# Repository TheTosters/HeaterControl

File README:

# Preamble
first instruction taken from:
https://github.com/Polidea/cmake-nRF5x
It is constantly changed and improved (or downproved :P)

# IMPORTANT:
Toolchain:
 * gcc-arm-none-eabi-8-2018-q4-major, or
 * gcc-arm-none-eabi-8-2019-q3-update-linux

NRF SDK:
 * nRF5_SDK_15.2.0_9412b96

You also need nrfprog tools and small patch for SDK from CMSIS.
But this is handled by preapre_env.sh

# To build & run tests...

This is super-glue solution, so your eyes will bleeed...
It will use host compiler (not cross-compiler) to build host based tests.
It is NOT ment to test all, only most complicated logic. So to have test build and run you have to:

execute:
cmake .. -DBUILD_TESTS=ON
make all

then you can call for example
./test/time_schedule_tests

# Manual patching SDK
But if you set C++17 then it fails :P You have to manualy patch NordicSDK (15.2)
and upgrade CMSIS to have things working go here
https://github.com/ARM-software/CMSIS_5

and download following files which should be placed here:
libarm_cortexM4lf_math.a, libarm_cortexM4l_math.a  ->  nordic_SDK_15.2/components/toolchain/cmsis/dsp/GCC
arm_cortexM4lf_math.lib  arm_cortexM4l_math.lib  ->  nordic_SDK_15.2/components/toolchain/cmsis/dsp/ARM

also copy folder 
CMSIS_5-develop/CMSIS/Core/Include  ->  nordic_SDK_15.2/components/toolchain/cmsis/include

clean & build all should work

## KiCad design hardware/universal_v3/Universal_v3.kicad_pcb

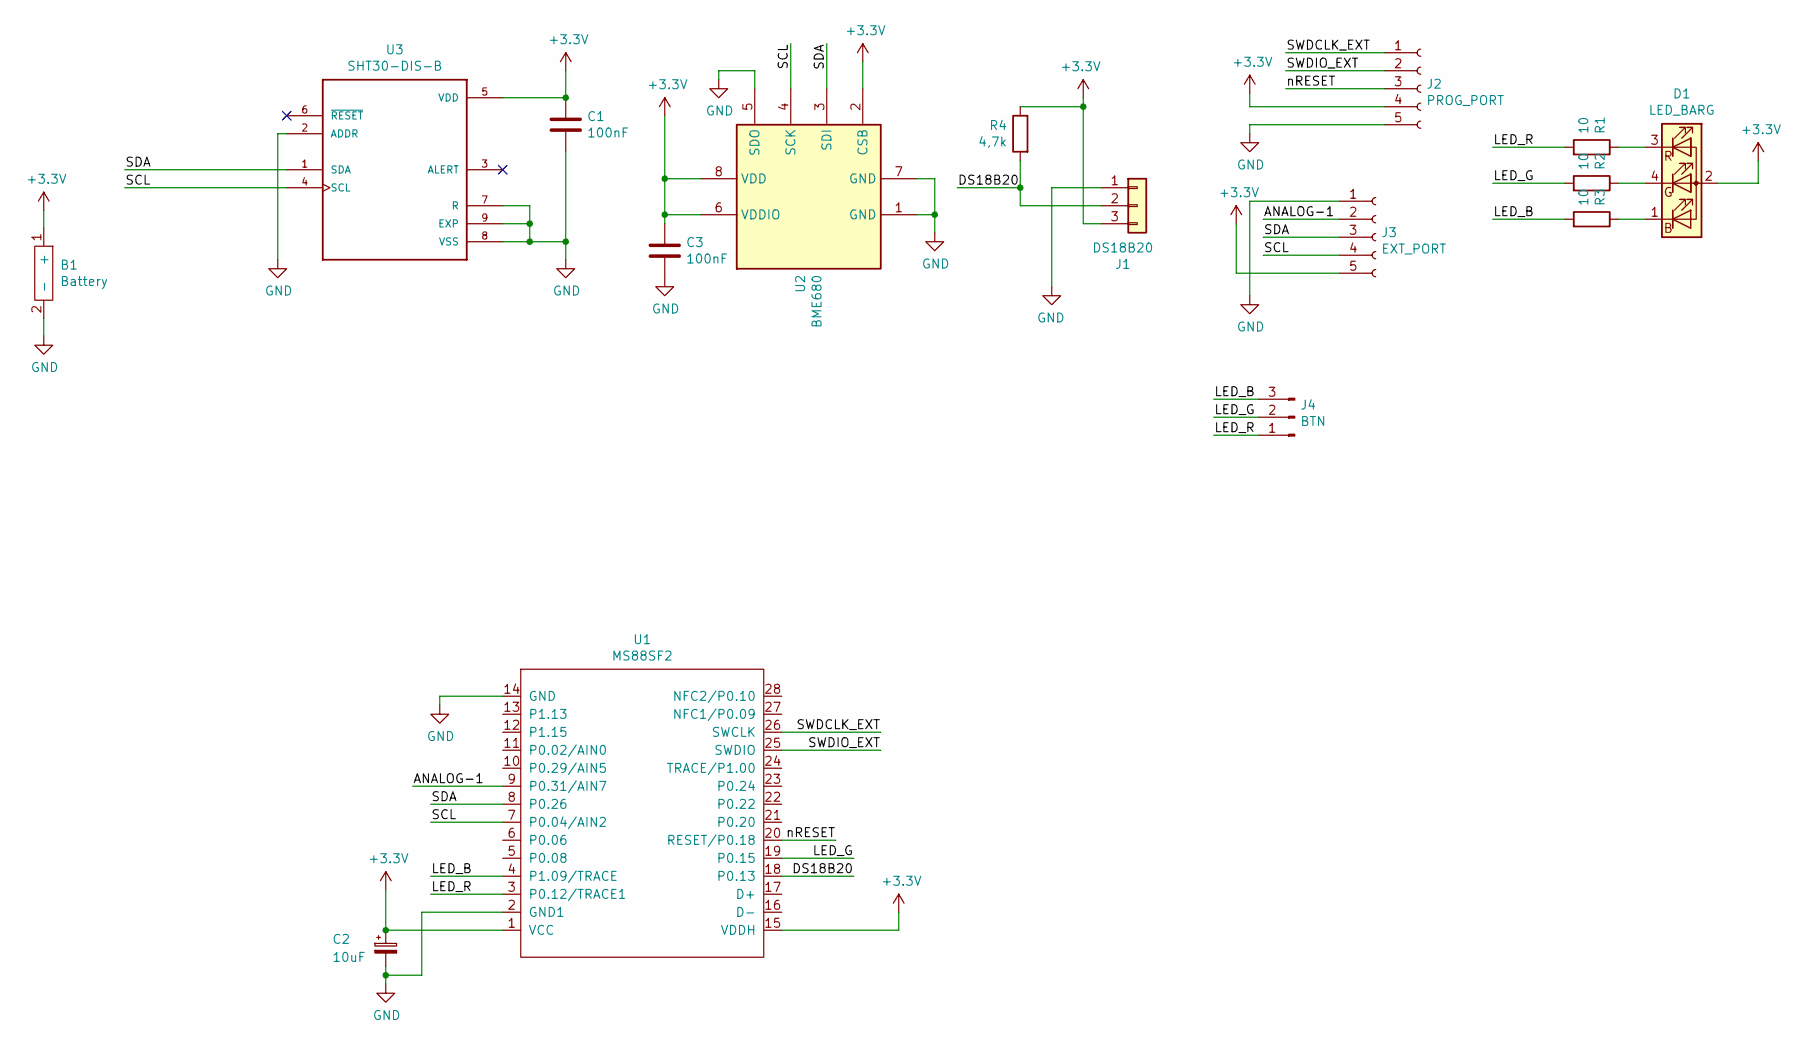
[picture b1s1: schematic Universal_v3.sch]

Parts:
B1: Battery; Cr2032-Holder
C1, C3: 100nF; C_0402_1005Metric
C2: 10uF; CP_EIA-2012-12_Kemet-R
D1: LED_BARG; Everlight_19-237_R6GHBHC-M07_2T
J1: DS18B20; 3Pads
J2: PROG_PORT; 5xPad
J3: EXT_PORT; 5xPad
J4: BTN; PinHeader_1x03_P2.54mm_Vertical
R1, R2, R3: 10; R_0402_1005Metric
R4: 4,7k; R_0402_1005Metric
U1: MS88SF2
U2: BME680; Bosch_LGA-8_3x3mm_P0.8mm_ClockwisePinNumbering
U3: SHT30-DIS-B; DFN250X250X100-9N

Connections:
+3V3: B1.1 (+), C1.1, C2.1, C3.1, D1.2 (A), J1.3, J2.4, J3.5, R4.1, U1.1 (VCC), U1.15 (VDDH), U2.2 (CSB), U2.6 (VDDIO), U2.8 (VDD), U3.5 (VDD)
/ANALOG-1: J3.2, U1.9 (P0.31/AIN7)
/DS18B20: J1.2, R4.2, U1.18 (P0.13)
/LED_B: J4.3, R3.2, U1.4 (P1.09/TRACE)
/LED_G: J4.2, R2.2, U1.19 (P0.15)
/LED_R: J4.1, R1.2, U1.3 (P0.12/TRACE1)
/SCL: J3.4, U1.7 (P0.04/AIN2), U2.4 (SCK), U3.4 (SCL)
/SDA: J3.3, U1.8 (P0.26), U2.3 (SDI), U3.1 (SDA)
/SWDCLK_EXT: J2.1, U1.26 (SWCLK)
/SWDIO_EXT: J2.2, U1.25 (SWDIO)
/nRESET: J2.3, U1.20 (RESET/P0.18)
GND: B1.2 (-), C1.2, C2.2, C3.2, J1.1, J2.5, J3.1, U1.2 (GND1), U1.14 (GND), U2.1 (GND), U2.5 (SDO), U2.7 (GND), U3.2 (ADDR), U3.7 (R), U3.8 (VSS), U3.9 (EXP)
unnamed: D1.1 (BK), R3.1
unnamed: D1.3 (RK), R1.1
unnamed: D1.4 (GK), R2.1

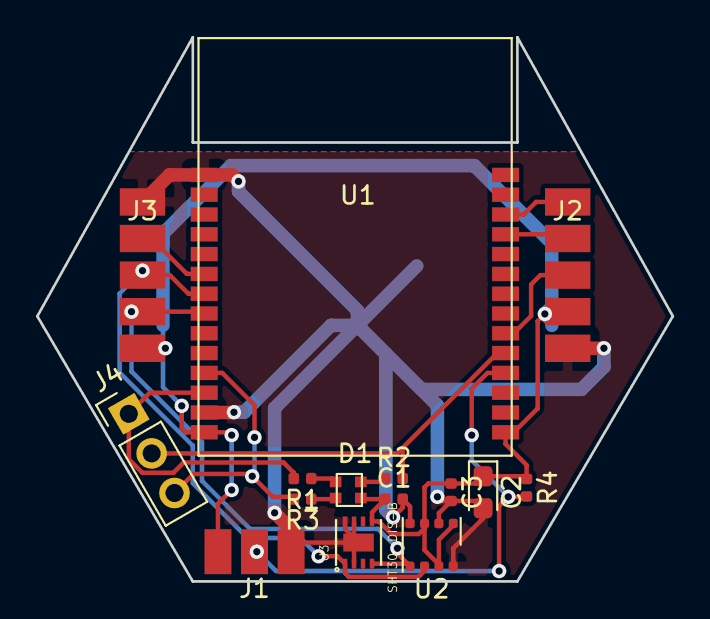
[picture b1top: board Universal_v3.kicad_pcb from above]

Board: 2 copper layers, 35.3 x 30.2 mm, 16 parts (1 on the bottom side), 15 nets.

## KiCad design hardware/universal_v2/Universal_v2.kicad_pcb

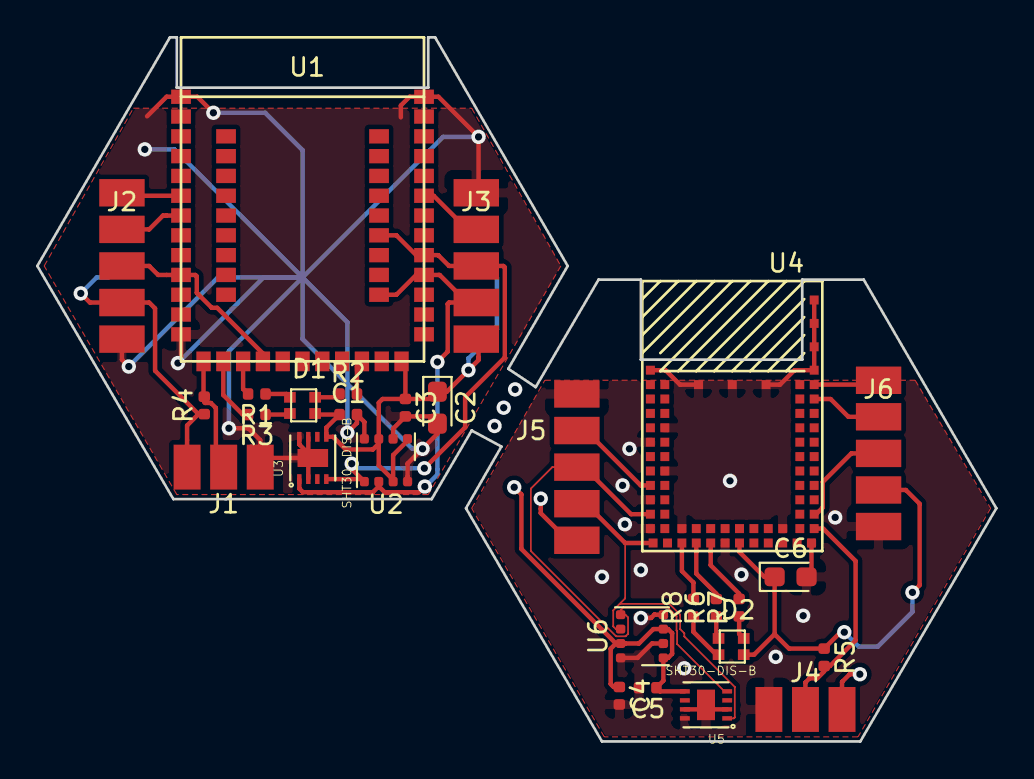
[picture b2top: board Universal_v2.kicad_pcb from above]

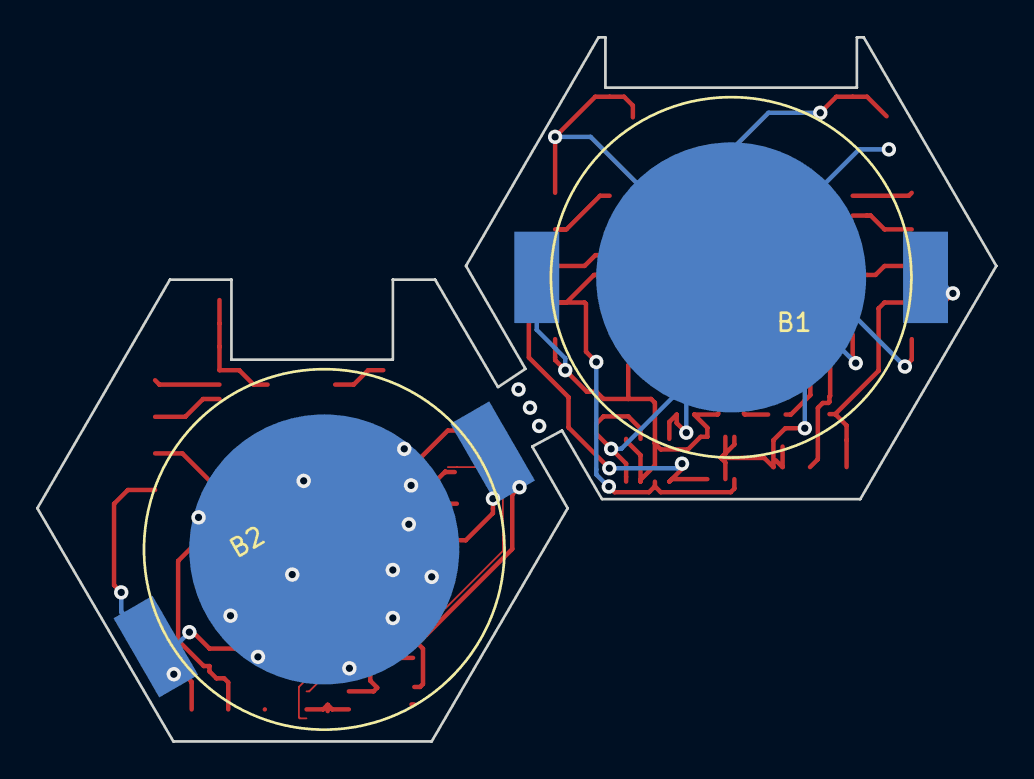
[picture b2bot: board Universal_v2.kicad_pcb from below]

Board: 2 copper layers, 53.3 x 39.1 mm, 30 parts (2 on the bottom side), 28 nets.

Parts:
B1, B2: Battery; Cr2032-Holder
C1, C3, C4, C5: 100nF; C_0402_1005Metric
C2, C6: 10uF; CP_EIA-2012-12_Kemet-R
D1, D2: LED_BARG; Everlight_19-237_R6GHBHC-M07_2T
J1, J4: DS18B20; 3Pads
J2, J6: PROG_PORT; 5xPad
J3, J5: EXT_PORT; 5xPad
R1, R2, R3, R6, R7, R8: 10; R_0402_1005Metric
R4, R5: 4,7k; R_0402_1005Metric
U1: HolyIot-18010; HolyIot_18010
U2, U6: BME680; Bosch_LGA-8_3x3mm_P0.8mm_ClockwisePinNumbering
U3, U5: SHT30-DIS-B; DFN250X250X100-9N
U4: BL654

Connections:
+3V3: B1.1, B2.1, C1.1, C2.1, C3.1, C4.1, C5.1, C6.1, D1.2, D2.2, J1.3, J2.4, J3.5, J4.3, J5.5, J6.4, R4.1, R5.1, U1.55, U2.2, U2.6, U2.8, U3.5, U4.31, U5.5, U6.2, U6.6, U6.8
/ANALOG-1: J3.2, U1.6
/DS18B20: J1.2, R4.2, U1.45
/LED_B: R3.2, U1.46
/LED_G: R2.2, U1.53
/LED_R: R1.2, U1.47
/Laird/ANALOG-1: J5.2, U4.49
/Laird/DS18B20: J4.2, R5.2, U4.21
/Laird/LED_B: R8.2, U4.39
/Laird/LED_G: R7.2, U4.35
/Laird/LED_R: R6.2, U4.37
/Laird/SCL: J5.3, U4.45, U5.4, U6.4
/Laird/SDA: J5.4, U4.42, U5.1, U6.3
/Laird/SWDCLK_EXT: J6.2, U4.3
/Laird/SWDIO_EXT: J6.1, U4.1
/Laird/nRESET: J6.3, U4.19
/SCL: J3.3, U1.9, U1.19, U2.4, U3.4
/SDA: J3.4, U1.10, U1.22, U2.3, U3.1
/SWDCLK_EXT: J2.2, U1.38
/SWDIO_EXT: J2.1, U1.37
/nRESET: J2.3, U1.41, U1.48
GND: B1.2, B2.2, C1.2, C2.2, C3.2, C4.2, C5.2, C6.2, J1.1, J2.5, J3.1, J4.1, J5.1, J6.5, U1.1, U1.32, U1.44, U2.1, U2.5, U2.7, U3.2, U3.7, U3.8, U3.9, U4.0, U4.23, U4.26, U4.33, U4.40, U4.43, U4.47, U4.52, U4.55, U4.58, U4.65, U4.66, U4.67, U4.68, U4.69, U4.70, U4.71, U5.2, U5.7, U5.8, U5.9, U6.1, U6.5, U6.7
unnamed: D1.1, R3.1
unnamed: D1.3, R1.1
unnamed: D1.4, R2.1
unnamed: D2.1, R8.1
unnamed: D2.3, R6.1
unnamed: D2.4, R7.1

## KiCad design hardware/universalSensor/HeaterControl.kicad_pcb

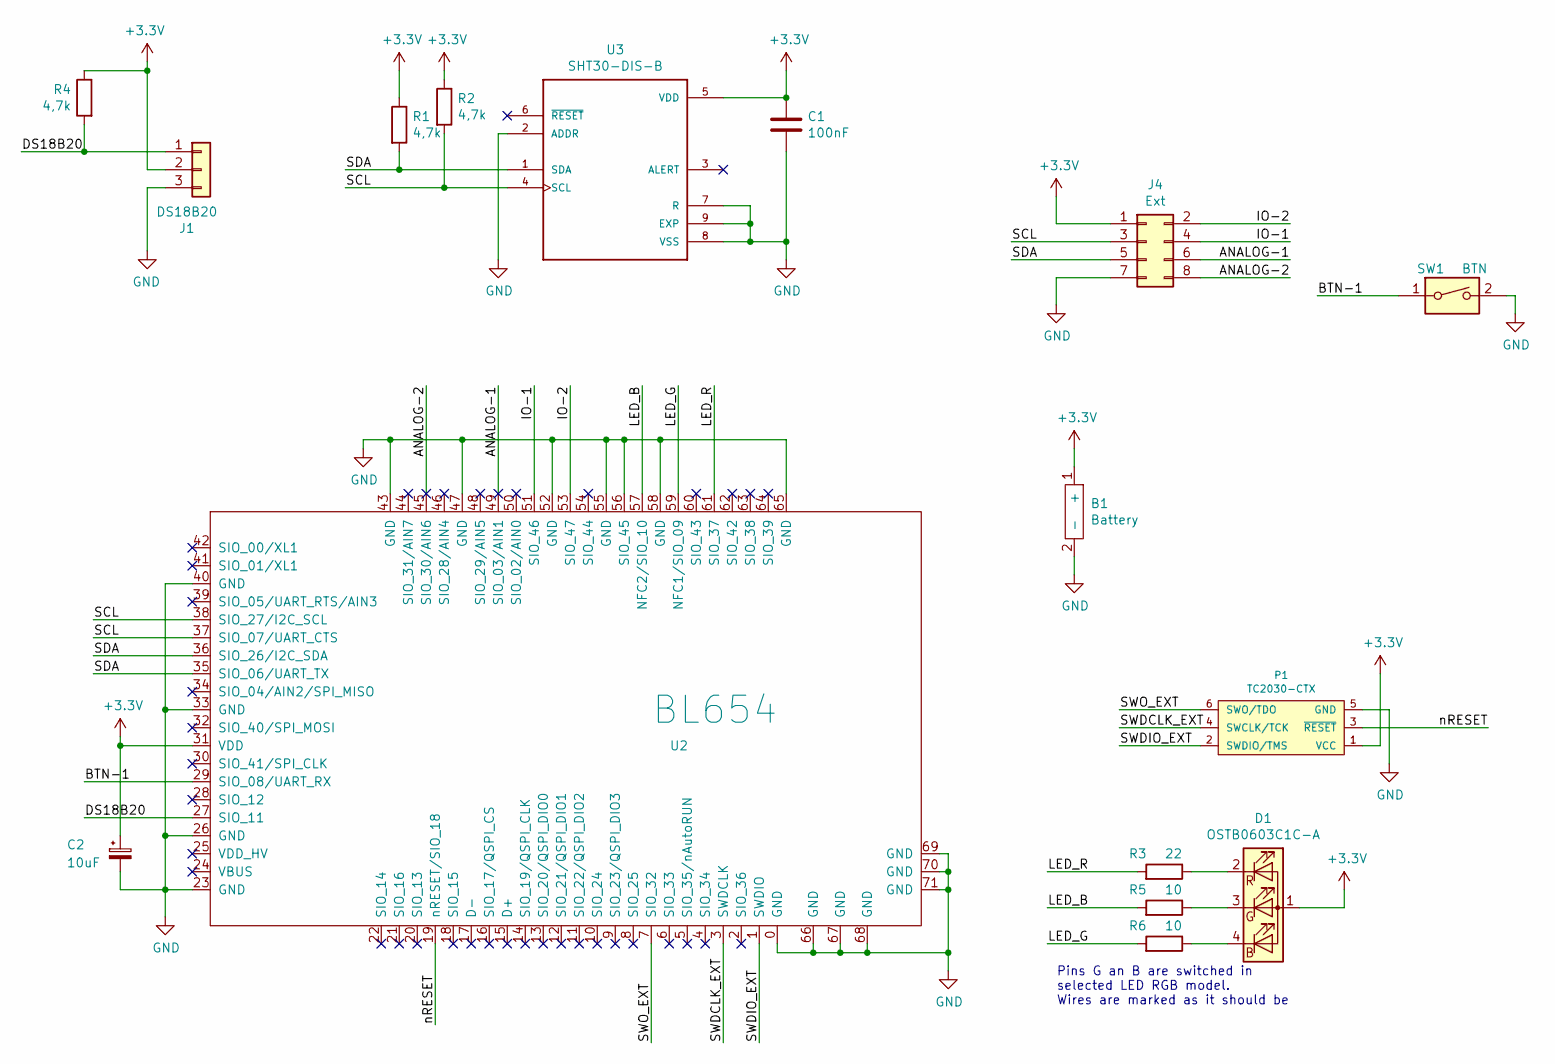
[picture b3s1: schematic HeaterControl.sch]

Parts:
B1: Battery; Cr2032-Holder
C1: 100nF; C_0402_1005Metric
C2: 10uF; CP_EIA-2012-12_Kemet-R
D1: OSTB0603C1C-A; LED_PACKAGE_1.6x1.5mm
J1: DS18B20; PinHeader_1x03_P2.54mm_Vertical_SMD_Pin1Left
J4: Ext; PinHeader_2x04_P1.00mm_Vertical_SMD
P1: TC2030-CTX; TC2030-NL_SMALL
R1, R2, R4: 4,7k; R_0402_1005Metric
R3: 22; R_0402_1005Metric
R5, R6: 10; R_0402_1005Metric
SW1: BTN; R_1206_3216Metric
U2: BL654
U3: SHT30-DIS-B; DFN250X250X100-9N

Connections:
+3V3: B1.1 (+), C1.1, C2.1, D1.1 (A), J1.2, J4.1, P1.1 (VCC), R1.1, R2.1, R4.1, U2.31 (VDD), U3.5 (VDD); also elsewhere on the board
/ANALOG-1: J4.6, U2.49 (SIO_03/AIN1)
/ANALOG-2: J4.8, U2.45 (SIO_30/AIN6)
/BTN-1: SW1.1, U2.29 (SIO_08/UART_RX)
/DS18B20: J1.1, R4.2, U2.27 (SIO_11)
/IO-1: J4.4, U2.51 (SIO_46)
/IO-2: J4.2, U2.53 (SIO_47)
/LED_B: R5.2, U2.57 (NFC2/SIO_10)
/LED_G: R6.2, U2.59 (NFC1/SIO_09)
/LED_R: R3.2, U2.61 (SIO_37)
/SCL: J4.3, R2.2, U2.37 (SIO_07/UART_CTS), U2.38 (SIO_27/I2C_SCL), U3.4 (SCL)
/SDA: J4.5, R1.2, U2.35 (SIO_06/UART_TX), U2.36 (SIO_26/I2C_SDA), U3.1 (SDA)
/SWDCLK_EXT: P1.4 (SWCLK/TCK), U2.3 (SWDCLK); also elsewhere on the board
/SWDIO_EXT: P1.2 (SWDIO/TMS), U2.1 (SWDIO); also elsewhere on the board
/SWO_EXT: P1.6 (SWO/TDO), U2.7 (SIO_32); also elsewhere on the board
/nRESET: P1.3 (~RESET~), U2.19 (nRESET/SIO_18); also elsewhere on the board
GND: B1.2 (-), C1.2, C2.2, J1.3, J4.7, P1.5 (GND), SW1.2, U2.0 (GND), U2.23 (GND), U2.26 (GND), U2.33 (GND), U2.40 (GND), U2.43 (GND), U2.47 (GND), U2.52 (GND), U2.55 (GND), U2.56 (SIO_45), U2.58 (GND), U2.65 (GND), U2.66 (GND), U2.67 (GND), U2.68 (GND), U2.69 (GND), U2.70 (GND), U2.71 (GND), U3.2 (ADDR), U3.7 (R), U3.8 (VSS), U3.9 (EXP); also elsewhere on the board
unnamed: D1.2 (RK), R3.1
unnamed: D1.3 (GK), R5.1
unnamed: D1.4 (BK), R6.1

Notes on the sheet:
Pins G an B are switched in selected LED RGB model. Wires are marked as it should be

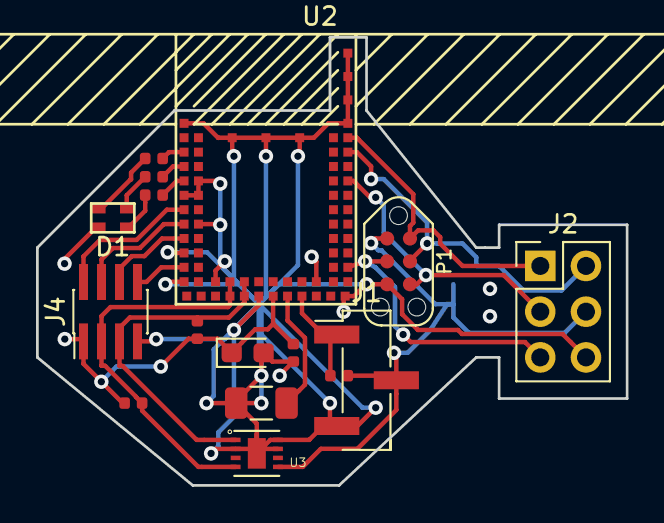
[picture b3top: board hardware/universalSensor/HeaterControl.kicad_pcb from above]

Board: 2 copper layers, 32.8 x 24.9 mm, 17 parts (1 on the bottom side), 20 nets.

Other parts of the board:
J2: DEV_PORT; PinHeader_2x03_P2.54mm_Vertical

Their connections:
+3V3: J2.4; also elsewhere on the board
/SWDCLK_EXT: J2.2; also elsewhere on the board
/SWDIO_EXT: J2.1; also elsewhere on the board
/SWO_EXT: J2.3; also elsewhere on the board
/nRESET: J2.5; also elsewhere on the board
GND: J2.6; also elsewhere on the board

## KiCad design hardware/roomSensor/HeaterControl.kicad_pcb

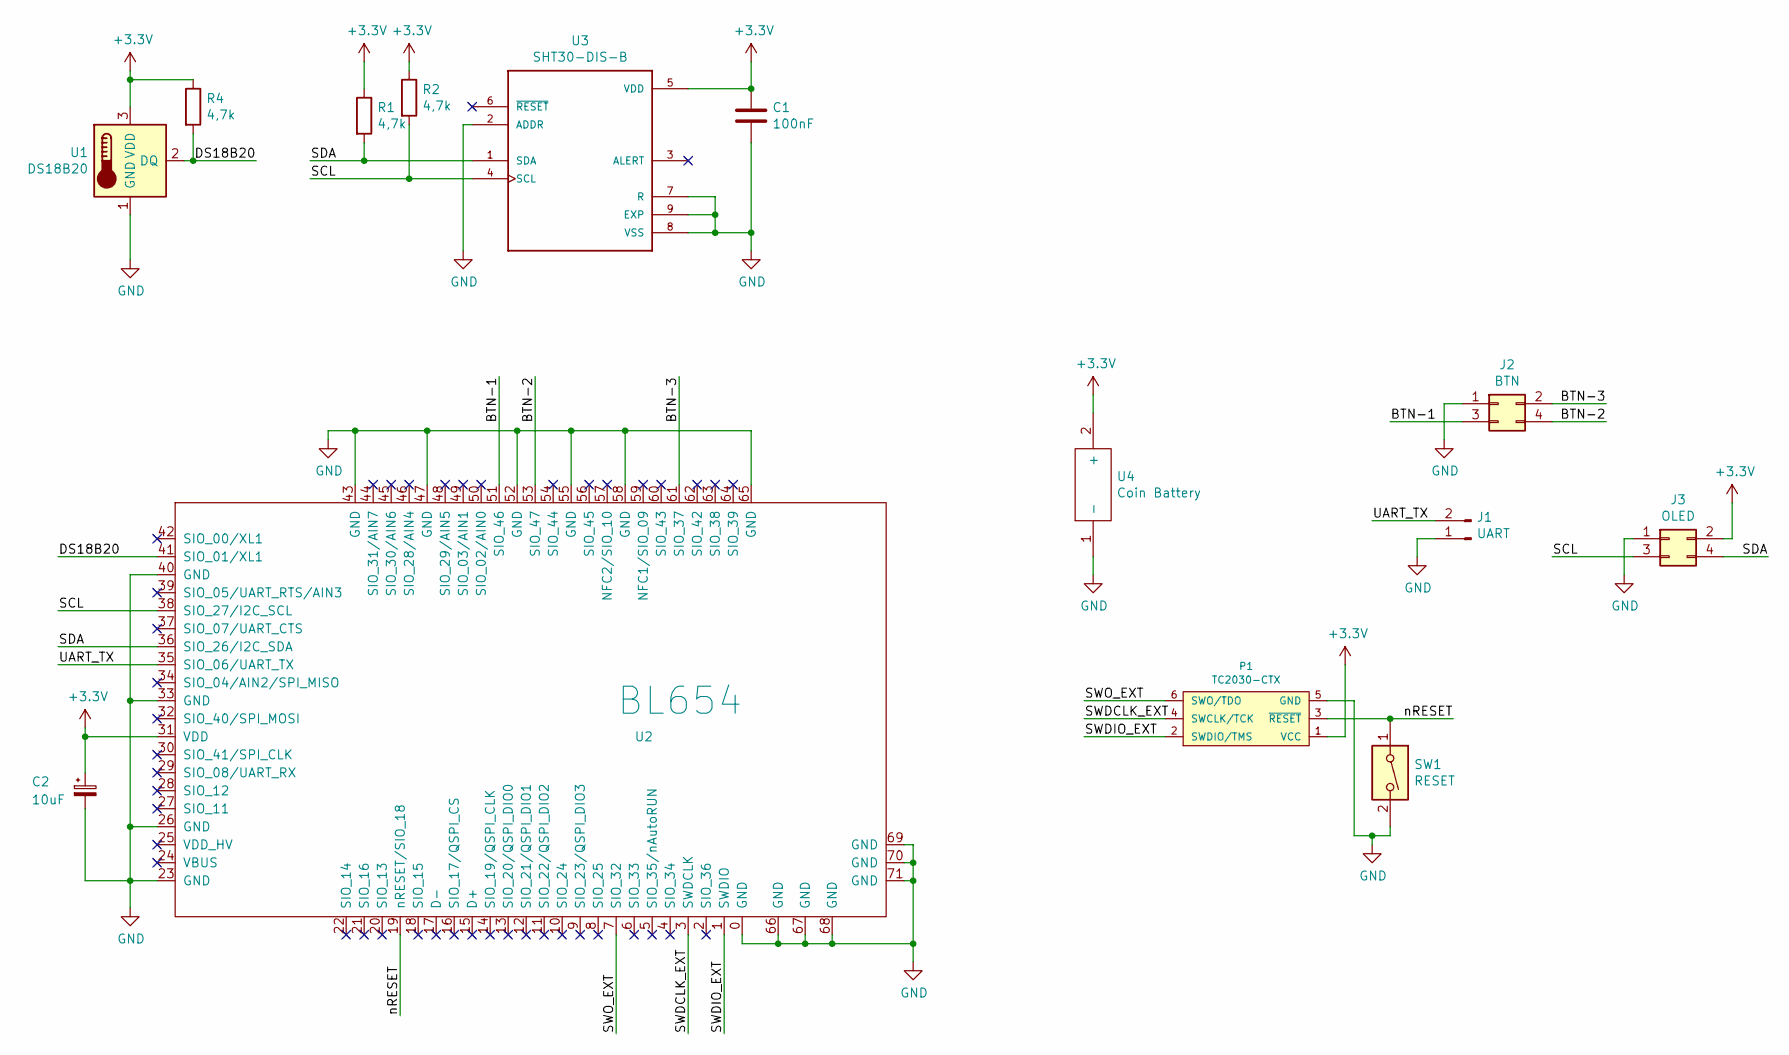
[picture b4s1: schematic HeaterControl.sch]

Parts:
C1: 100nF; C_0603_1608Metric
C2: 10uF; CP_EIA-2012-12_Kemet-R
J1: UART; PinHeader_1x02_P2.54mm_Vertical
J2: BTN; PinHeader_2x02_P2.54mm_Vertical
J3: OLED; PinHeader_2x02_P2.54mm_Vertical
P1: TC2030-CTX; TC2030-NL_SMALL
R1, R2, R4: 4,7k; R_1206_3216Metric
SW1: RESET; R_1206_3216Metric
U1: DS18B20; TO-92_Inline
U2: BL654
U3: SHT30-DIS-B; DFN250X250X100-9N
U4: Coin Battery; BS3; Manufacturer_Part_Number BS-3

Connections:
+3V3: C1.1, C2.1, J3.2, P1.1 (VCC), R1.1, R2.1, R4.1, U1.3 (VDD), U2.31 (VDD), U3.5 (VDD), U4.2 (+)
/BTN-1: J2.3, U2.51 (SIO_46)
/BTN-2: J2.4, U2.53 (SIO_47)
/BTN-3: J2.2, U2.61 (SIO_37)
/DS18B20: R4.2, U1.2 (DQ), U2.41 (SIO_01/XL1)
/SCL: J3.3, R2.2, U2.38 (SIO_27/I2C_SCL), U3.4 (SCL)
/SDA: J3.4, R1.2, U2.36 (SIO_26/I2C_SDA), U3.1 (SDA)
/SWDCLK_EXT: P1.4 (SWCLK/TCK), U2.3 (SWDCLK)
/SWDIO_EXT: P1.2 (SWDIO/TMS), U2.1 (SWDIO)
/SWO_EXT: P1.6 (SWO/TDO), U2.7 (SIO_32)
/UART_TX: J1.2, U2.35 (SIO_06/UART_TX)
/nRESET: P1.3 (~RESET~), SW1.1, U2.19 (nRESET/SIO_18)
GND: C1.2, C2.2, J1.1, J2.1, J3.1, P1.5 (GND), SW1.2, U1.1 (GND), U2.0 (GND), U2.23 (GND), U2.26 (GND), U2.33 (GND), U2.40 (GND), U2.43 (GND), U2.47 (GND), U2.52 (GND), U2.55 (GND), U2.58 (GND), U2.65 (GND), U2.66 (GND), U2.67 (GND), U2.68 (GND), U2.69 (GND), U2.70 (GND), U2.71 (GND), U3.2 (ADDR), U3.7 (R), U3.8 (VSS), U3.9 (EXP), U4.1 (-)

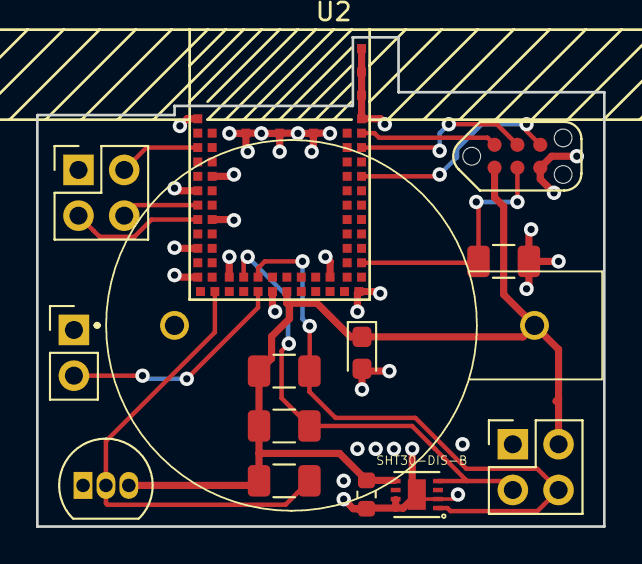
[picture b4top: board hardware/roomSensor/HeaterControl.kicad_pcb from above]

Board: 2 copper layers, 31.5 x 27.2 mm, 14 parts (0 on the bottom side), 13 nets.

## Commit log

2019-03-24 First version of hardware
2019-03-28 initial version
2019-03-28 Fix draw library, add ds18b20 measurements
2019-03-29 add custom boards, improved build system
2019-03-29 Buttons stub now works
2019-03-30 Add missing hardware parts
2019-04-01 Fix build scripts, add display abstraction
2019-04-02 New DS18b20 port, integration of DS support into upper abstraction
2019-04-02 Add BTLE advertising of data, not finished
2019-04-03 Add arial font data
2019-04-03 Add base for classes which uses timer
2019-04-03 Increased advert count on btle
2019-04-03 Add calendar class
2019-04-03 Add function to draw xbm bitmaps
2019-04-04 Add xbm icon wrapping class
2019-04-04 Improved fonts bridge
2019-04-04 Restructure of folders
2019-04-04 Moved implementation from cpp to h
2019-04-04 Reverted init list approach
2019-04-04 Add default screen renderer
2019-04-04 Add observer pattern
2019-04-04 Update notes about how to compile on gcc 8
2019-04-05 try to use cmake configuration from plant
2019-04-05 cleanup
2019-04-05 C++17 enabled, add screen stack support
2019-04-05 DONE!
2019-04-09 add sht30 library
2019-04-09 used tempC type in sensors
2019-04-10 - moved unit to separete class - typenapes changed to upper case - fixed temperature comparision in sensors
2019-04-10 added unit to ds
2019-04-10 fixed flashing on Windows
2019-04-11 - fixed crc calculating - fixed reading twi
2019-04-11 - disabled ds
2019-04-11 Add main thread dispatcher
2019-04-11 Fixes for merge
2019-04-11 Update of cmake for windows/linux hosts
2019-04-11 - generalization of sensors usage
2019-04-11 moved timing const to specific sensors
2019-04-11 Making BTLE advert working
2019-04-11 sensors factory and unification with other parts of code
2019-04-11 cleanup + fix for merge
2019-04-11 Trait based factory for sensors
2019-04-12 removed power on/off on hardware sensors/oled
2019-04-12 Reworked display power management and screen stack rendering
2019-04-12 Reworked power management cycle on sensors
2019-04-12 Add display of humidity if avail on default screen
2019-04-12 Reworked observer subsystem. Add status screen
2019-04-13 Removed Sensor/Oled PWR circuts
2019-04-13 Labels on PCB rearanged
2019-04-13 Add another schematic, add capacitor and rework 3v3 on laird
2019-04-15 status screen ready, fixes in observable
2019-04-16 Suppress ABI note for gcc 7.1
2019-04-16 - calendar modified - added weekUnit - partiatly done temperatureSheduler
2019-04-16 remove dependency to ctime
2019-04-16 Start work of integration heating plan
2019-04-16 Add heating model, still under work
2019-04-17 PCB layout fo reciever
2019-04-17 - add all functionalities to temperatureSheduler
2019-04-17 Changes after review, part 1
2019-04-19 Fix in hardwary library paths
2019-04-19 second part of review fixes
2019-04-19 Add gtest support
2019-04-19 Add temp alias tests
2019-04-19 Add first test for alias and period. Fix for period handling
2019-04-23 Additional tests
2019-04-23 Fix for removeAlias
2019-04-23 Fix test setOverlapingPeriod
2019-04-23 Fix wrong tests
2019-04-24 Add splitPeriodByRange and removePeriodsInRange + tests
2019-04-24 Add truncation functions + tests
2019-04-24 Rename method removeTemperaturePeriod to removePeriodAt
2019-04-24 Add merge periods + tests
2019-04-24 Fixes to make test passing
2019-04-24 Code cleanup
2019-04-25 Reorganisation of BT layer
2019-04-25 Compilation fix
2019-04-29 Bluetooth stack first version, under work
2019-04-30 New build system
2019-05-04 First steps with btle characteristics
2019-05-04 Refactor of structure
2019-05-05 Add warning susp. for gcc > 7.1
2019-05-05 Next stages of BTLE charact. implementation
2019-05-05 More generic bte characteristic
2019-05-06 Refactors, bug fixing, still not stable
2019-05-07 Warning fixes
2019-05-07 gatt stack + char + services almost stable
2019-05-07 Sensor values are propageted to GATT, notification still not working
2019-05-07 Working BLE notifications
2019-05-07 code celanup
2019-05-08 cleanup, temp stability fix (disabled flash), reenabling advert
2019-05-09 add humitidy charact., introduced custom & BT.org type of services
2019-05-09 Add bluetooth mode selector
2019-05-09 Add remote configuration screen
2019-05-10 New BT characteristic and services
2019-05-10 Compilation fixes, added services to stack
2019-05-10 changes in characteristic type hierarchy, linked GATT to Sensors
2019-05-10 refactor of code
2019-05-14 Add characteristic write support, some characteristic are forbiden to use, service refactor
2019-06-19 Add prod dev required defines, add battery level
2019-09-01 Week schedule builder
2019-09-07 Prepare env script
2019-09-07 Prepare env
2019-09-07 Make things compile again
2019-09-07 Rename
2019-09-07 Reanme to markdown
2019-09-07 revert
2019-09-07 Refactor of structure, exposed communiaction
2019-09-10 New universal sensor board
2019-09-10 Removal unused file
2019-09-12 making things work again
2019-09-16 next elements bring back to life
2019-09-17 Experimental integration with butonless DFU
2019-10-07 Add RGB Led support, and universal board definition
2019-10-09 Add dev port do univeral board
2019-10-09 Add measure on deman, configuration more exposed, changed btle advert behavior
2019-10-09 Add Green diode indication on measure on demand
2019-10-09 Add error handler
2019-10-13 RGB led emulation class
2019-11-03 Universal board v2
2019-11-06 Another version of hardware concept
2019-12-11 Hardware v2, upgrade
2019-12-12 Final hardware version 2
2019-12-12 Fixed mechanical shape
2019-12-28 (WIP) Refactor of build system
2019-12-28 RGB leds now compiles for NONE variant
2019-12-28 Improvement to logging
2019-12-28 Some random changes and cleanups
2020-01-31 Hardveare Universal_v3 created
2020-01-31 add missing library
